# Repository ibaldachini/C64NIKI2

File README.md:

**C64NIKI2** is a project to rebuild Commodore 64 Italian NIKI 2 cartridge.  
It has KiCad 7 project with schematic and PCB.  
Also there is a SolveSpace 3D project for cartridge case with holes for the two buttons.

**Contents**

- C64NIKI2.kicad_pro: this is the KiCad 7 project with schematic and PCB
- C64NIKI2.zip: this is a zip file with all needed files to print PCB (all gerber, drill and edge cuts files also present in this repo, but all in one file)
- C64NIKI2-Manuale-Utente.pdf: Italian user manual for NIKI 2 cartridge
- COVER-BOTTOM: bottom part of cartridge case, SolveSpace and stl files
- COVER-TOP: top part of cartridge case, SolveSpace and stl files
- C64NIKI2.csv, C64NIKI2-bom.odt: bom files, first export from KiCad, second is a libreoffice file with bom in leaflet format
- C64NIKIII-etichetta-CARTRIDGE: libreoffice and pdf file with cartidge label to print and paste on cartridge case
- C64-Cart-NoSilkS.kicad_mod: C64 cartidge connector from https://github.com/hackup/64kCart

**License**

Shield: [![CC BY-NC-SA 4.0][cc-by-nc-sa-shield]][cc-by-nc-sa]

This work is licensed under a
[Creative Commons Attribution-NonCommercial-ShareAlike 4.0 International License][cc-by-nc-sa].

[![CC BY-NC-SA 4.0][cc-by-nc-sa-image]][cc-by-nc-sa]

[cc-by-nc-sa]: http://creativecommons.org/licenses/by-nc-sa/4.0/
[cc-by-nc-sa-image]: https://licensebuttons.net/l/by-nc-sa/4.0/88x31.png
[cc-by-nc-sa-shield]: https://img.shields.io/badge/License-CC%20BY--NC--SA%204.0-lightgrey.svg

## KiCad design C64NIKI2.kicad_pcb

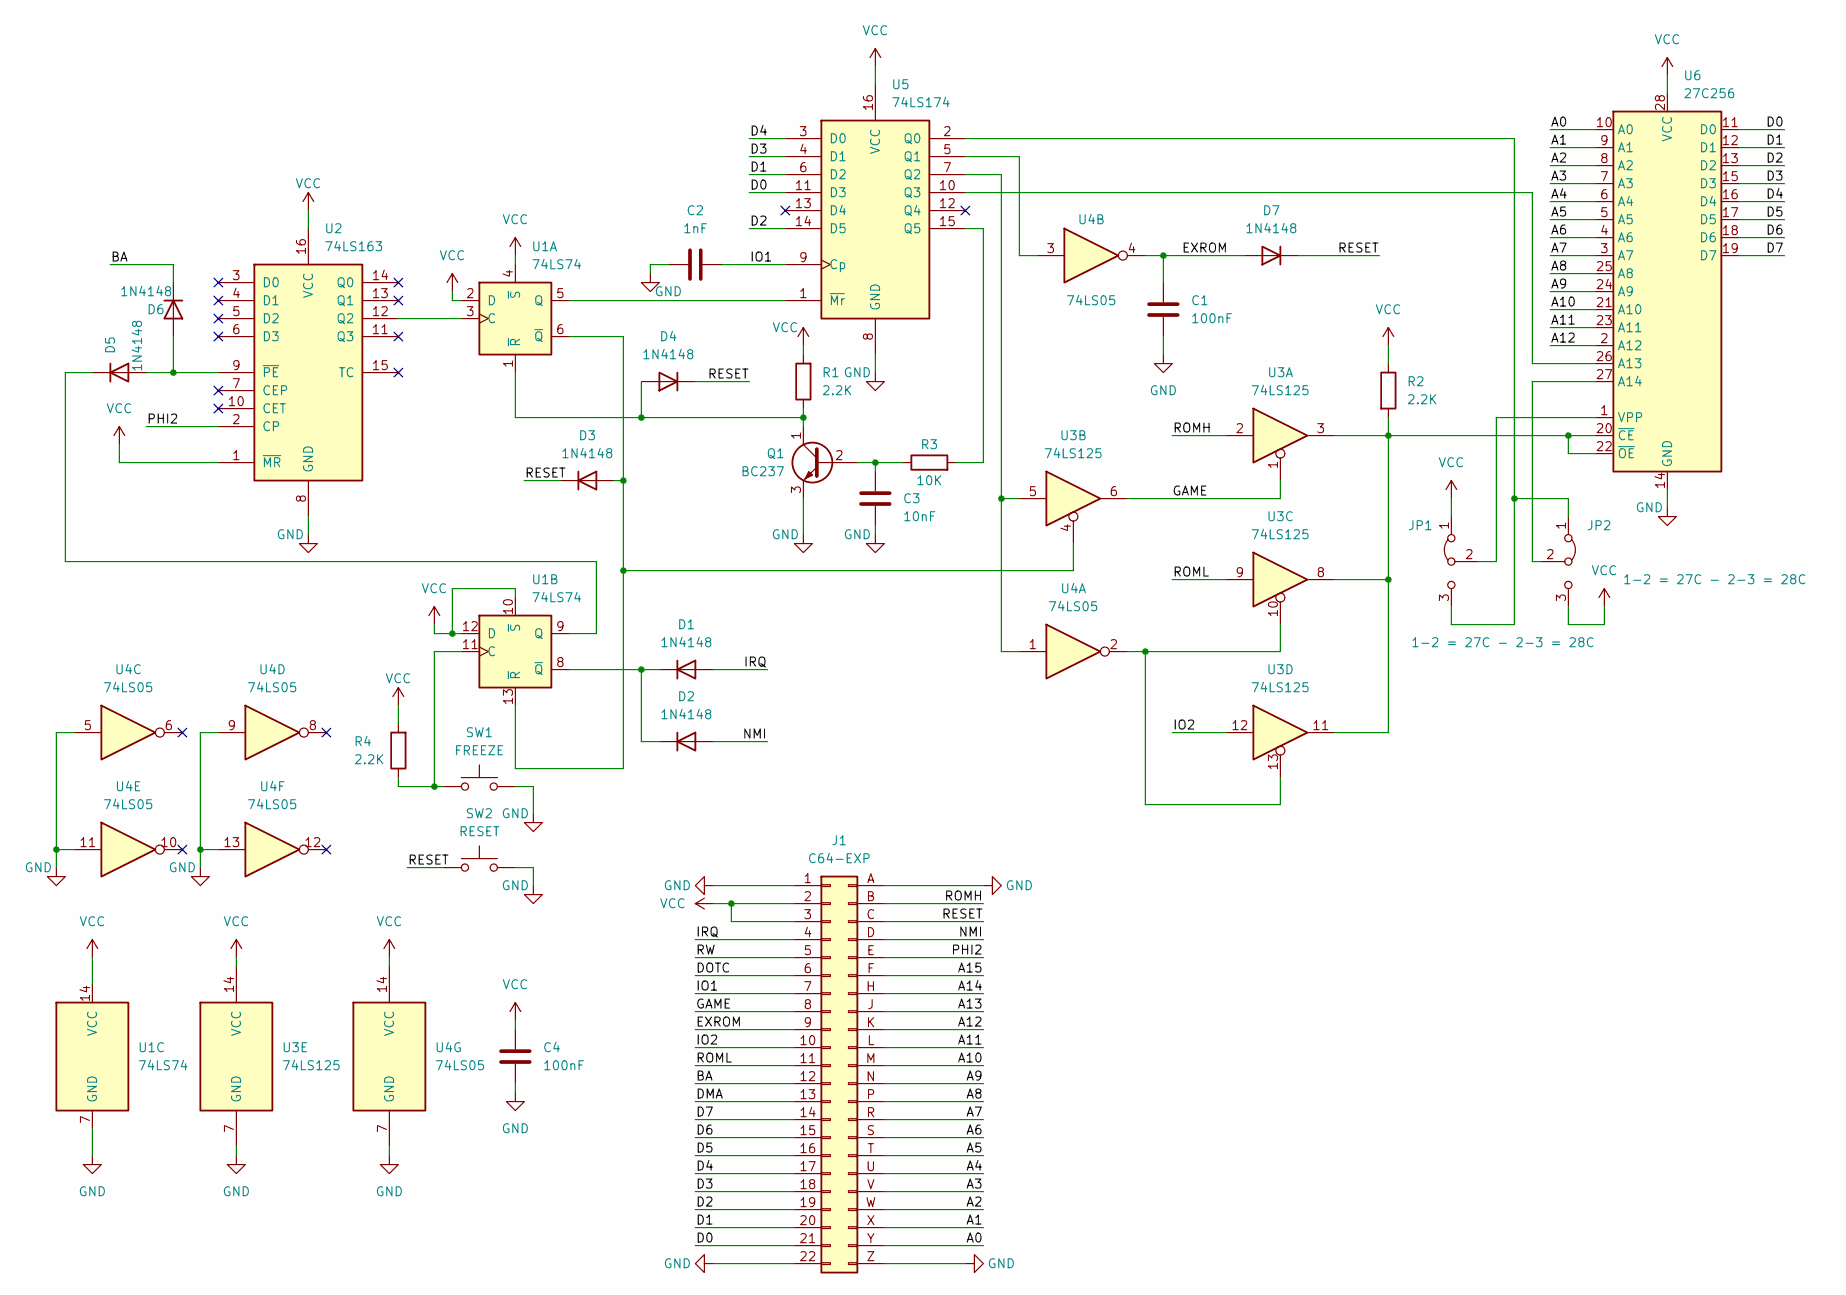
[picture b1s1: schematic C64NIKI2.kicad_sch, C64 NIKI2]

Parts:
C1, C4: 100nF; C_Disc_D4.3mm_W1.9mm_P5.00mm
C2: 1nF; C_Disc_D4.3mm_W1.9mm_P5.00mm
C3: 10nF; C_Disc_D4.3mm_W1.9mm_P5.00mm
D1, D2, D3, D4, D5, D6, D7: 1N4148; D_DO-35_SOD27_P10.16mm_Horizontal
J1: C64-EXP; C64-Cart-NoSilkS
JP1, JP2: 1-2 = 27C - 2-3 = 28C; BottomSolderJumper-3_P1.3mm_Bridged2Bar12_Pad1.0x1.5mm_Numb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
Q1: BC237; TO-92_Wide
R1, R2, R4: 2.2K; R_Axial_DIN0207_L6.3mm_D2.5mm_P10.16mm_Horizontal
R3: 10K; R_Axial_DIN0207_L6.3mm_D2.5mm_P10.16mm_Horizontal
SW1: FREEZE; NIKI2-Button
SW2: RESET; NIKI2-Button
U1: 74LS74; DIP-14_W7.62mm_Socket
U2: 74LS163; DIP-16_W7.62mm_Socket
U3: 74LS125; DIP-14_W7.62mm_Socket
U4: 74LS05; DIP-14_W7.62mm_Socket
U5: 74LS174; DIP-16_W7.62mm_Socket
U6: 27C256; DIP-28_W15.24mm

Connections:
/A0: J1.Y, U6.10 (A0)
/A1: J1.X, U6.9 (A1)
/A2: J1.W, U6.8 (A2)
/A3: J1.V, U6.7 (A3)
/A4: J1.U, U6.6 (A4)
/A5: J1.T, U6.5 (A5)
/A6: J1.S, U6.4 (A6)
/A7: J1.R, U6.3 (A7)
/A8: J1.P, U6.25 (A8)
/A9: J1.N, U6.24 (A9)
/A10: J1.M, U6.21 (A10)
/A11: J1.L, U6.23 (A11)
/A12: J1.K, U6.2 (A12)
/A13: J1.J
/A14: J1.H
/A15: J1.F
/BA: D6.1 (K), J1.12
/D0: J1.21, U5.11 (D3), U6.11 (D0)
/D1: J1.20, U5.6 (D2), U6.12 (D1)
/D2: J1.19, U5.14 (D5), U6.13 (D2)
/D3: J1.18, U5.4 (D1), U6.15 (D3)
/D4: J1.17, U5.3 (D0), U6.16 (D4)
/D5: J1.16, U6.17 (D5)
/D6: J1.15, U6.18 (D6)
/D7: J1.14, U6.19 (D7)
/DMA: J1.13
/DOTC: J1.6
/EXROM: C1.1, D7.2 (A), J1.9, U4.4
/GAME: J1.8, U3.1, U3.6
/IO1: C2.2, J1.7, U5.9 (Cp)
/IO2: J1.10, U3.12
/IRQ: D1.2 (A), J1.4
/NMI: D2.2 (A), J1.D
/PHI2: J1.E, U2.2 (CP)
/RESET: D3.1 (K), D4.1 (K), D7.1 (K), J1.C, SW2.1
/ROMH: J1.B, U3.2
/ROML: J1.11, U3.9
/RW: J1.5
GND: C1.2, C2.1, C3.2, C4.2, J1.1, J1.22, J1.A, J1.Z, Q1.3 (E), SW1.2, SW2.2, U1.7 (GND), U2.8 (GND), U3.7 (GND), U4.5, U4.7 (GND), U4.9, U4.11, U4.13, U5.8 (GND), U6.14 (GND)
unnamed: D1.1 (K), D2.1 (K), U1.8 (~Q)
unnamed: D3.2 (A), U1.6 (~Q), U1.13 (~R), U3.4
unnamed: D4.2 (A), Q1.1 (C), R1.1, U1.1 (~R)
unnamed: D5.2 (A), D6.2 (A), U2.9 (~PE)
unnamed: D5.1 (K), U1.9 (Q)
unnamed: JP1.3 (B), JP2.1 (A), U5.2 (Q0)
unnamed: JP1.2 (C), U6.1 (VPP)
unnamed: JP2.2 (C), U6.27 (A14)
unnamed: C3.1, Q1.2 (B), R3.1
unnamed: U1.3 (C), U2.12 (Q2)
unnamed: U1.5 (Q), U5.1 (~Mr)
unnamed: R4.1, SW1.1, U1.11 (C)
unnamed: U3.10, U3.13, U4.2
unnamed: U4.3, U5.5 (Q1)
unnamed: U3.5, U4.1, U5.7 (Q2)
unnamed: U5.10 (Q3), U6.26 (A13)
unnamed: R3.2, U5.15 (Q5)
unnamed: R2.2, U3.3, U3.8, U3.11, U6.20 (~CE), U6.22 (~OE)
VCC: C4.1, J1.2, J1.3, JP1.1 (A), JP2.3 (B), R1.2, R2.1, R4.2, U1.2 (D), U1.4 (~S), U1.10 (~S), U1.12 (D), U1.14 (VCC), U2.1 (~MR), U2.16 (VCC), U3.14 (VCC), U4.14 (VCC), U5.16 (VCC), U6.28 (VCC)

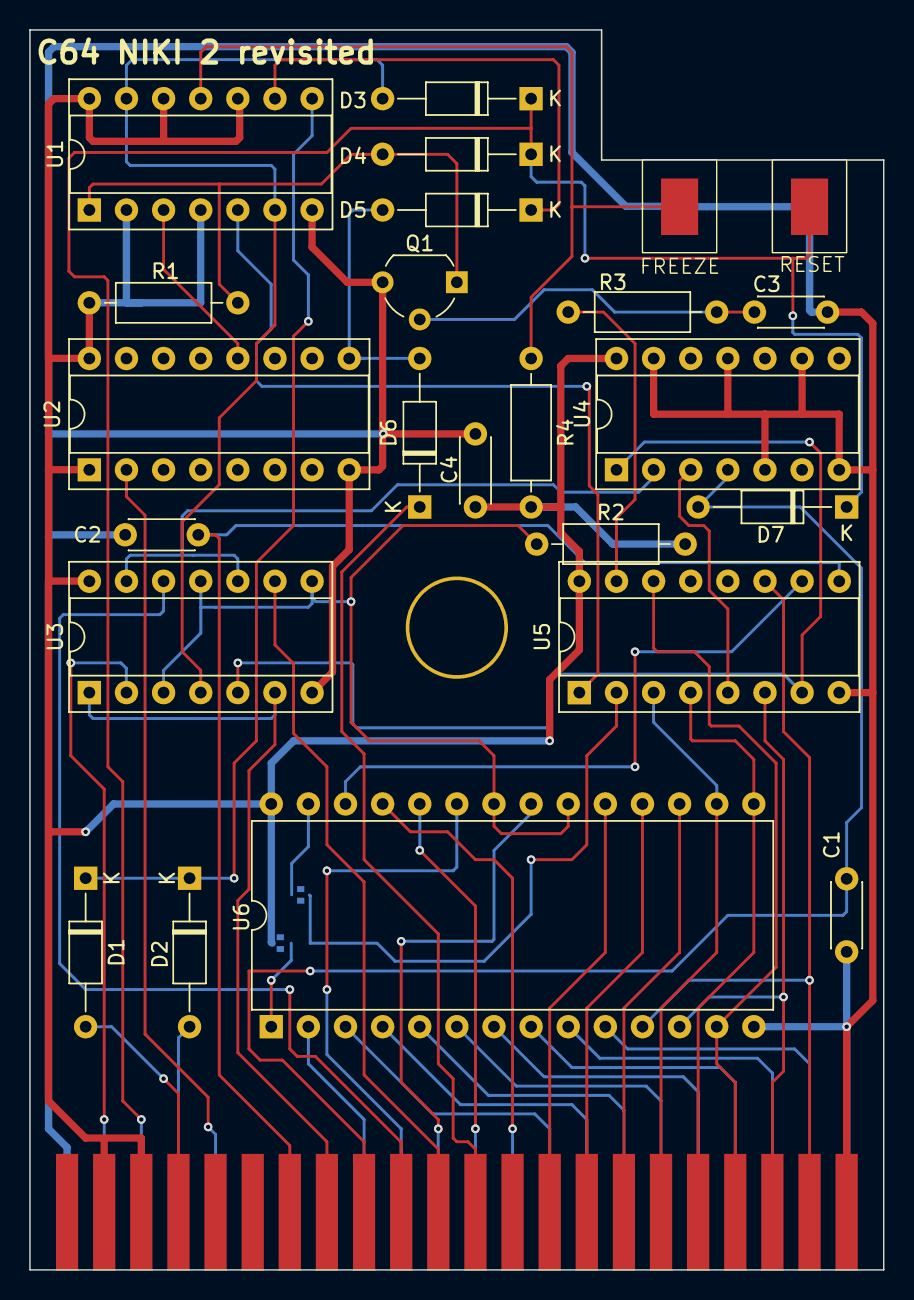
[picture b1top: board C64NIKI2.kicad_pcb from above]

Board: 2 copper layers, 58.4 x 84.8 mm, 27 parts (0 on the bottom side), 52 nets.

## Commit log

2024-01-08 work in progress
2024-01-10 complete net
2024-01-12 first release
2024-01-13 First printed revision
2024-01-16 First real printed to pcbway
2024-02-03 Fixed JP1 and JP2 silk screen
2024-02-06 added 3d print and labels
2024-02-07 Added user manual
2024-02-07 first readme with license
2024-02-07 readme updated
2024-02-07 cleanup
2024-10-02 updated case
